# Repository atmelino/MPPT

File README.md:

# MPPT
Maximum Power Point Tracking Solar Powered Computer 

https://atmelino.github.io/MPPT/

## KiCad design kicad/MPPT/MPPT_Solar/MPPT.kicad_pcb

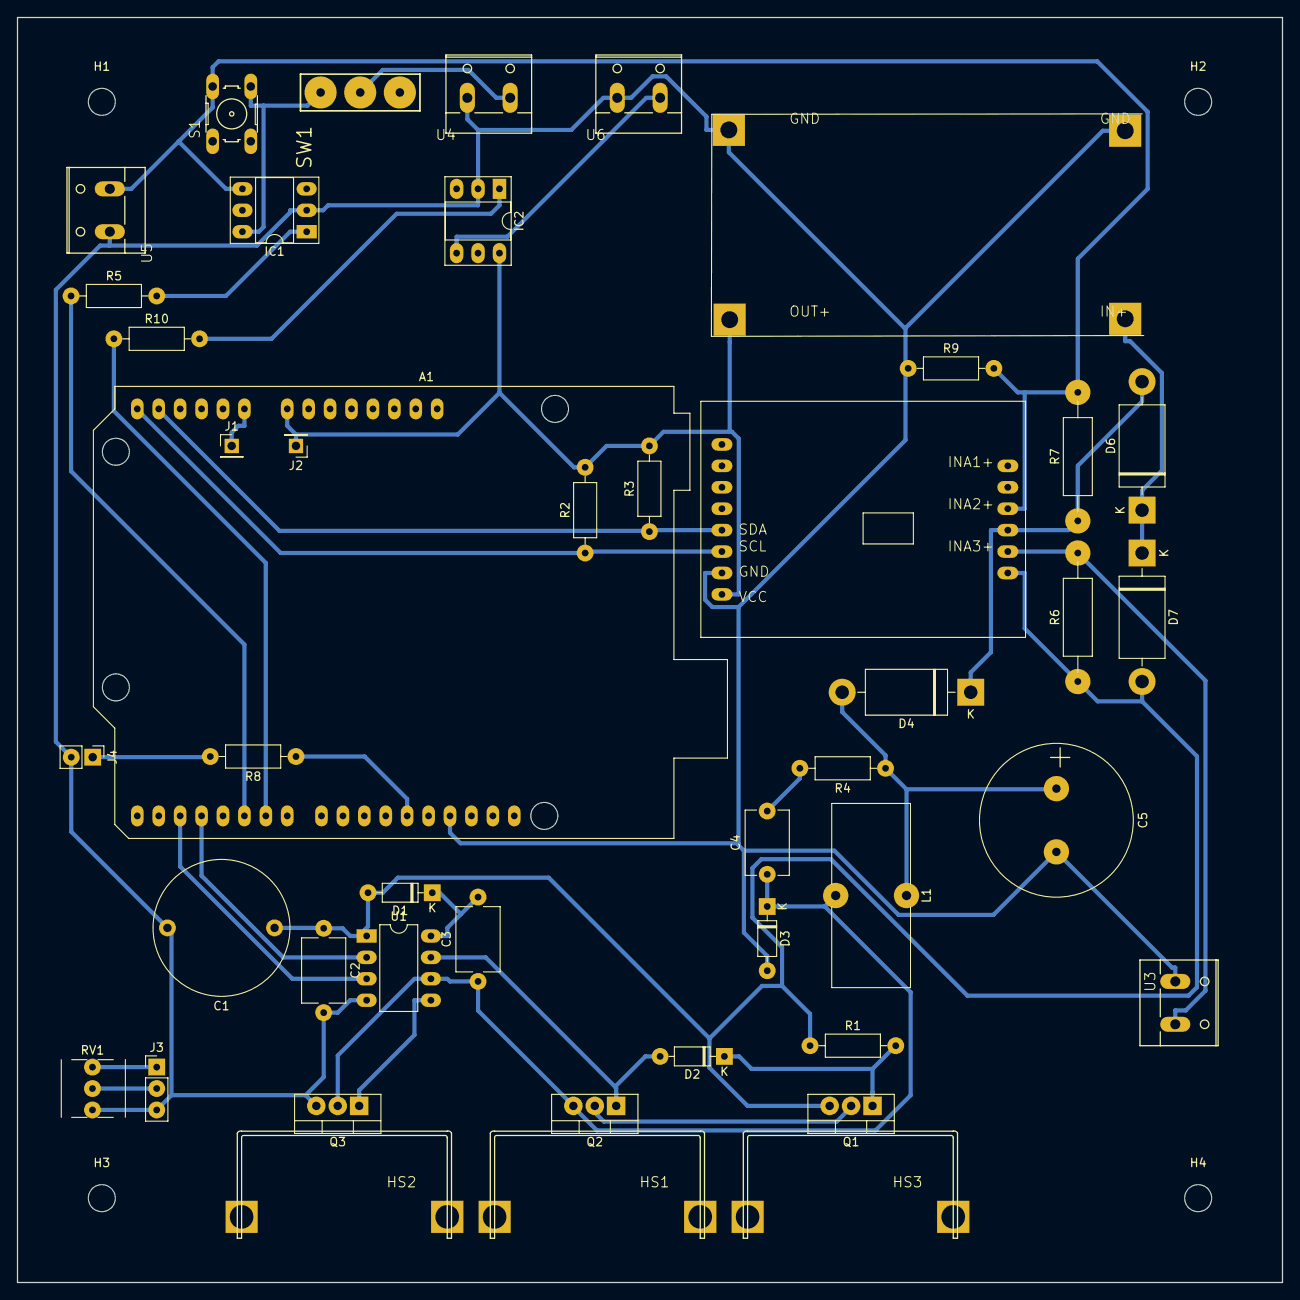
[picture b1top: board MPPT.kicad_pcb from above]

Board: 2 copper layers, 150.0 x 150.0 mm, 49 parts (0 on the bottom side), 31 nets.

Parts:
A1: Arduino_UNO_R3_mylib; Arduino_UNO_R3
C1: 1000uF/25V; C_Radial_D16.0mm_H25.0mm_P7.50mm_mod
C2, C3: 0.1uF; C_Disc_D7.5mm_W5.0mm_P10.00mm
C4: 0.1uF; C_Disc_D7.5mm_W5.0mm_P7.50mm
C5: 220uF/25V; C_Radial_D18.0mm_H35.5mm_P7.50mm
D1, D3: 1N4007; D_DO-35_SOD27_P7.62mm_Horizontal_fatpad
D2: 1N4148; D_DO-35_SOD27_P7.62mm_Horizontal_fatpad
D4, D6, D7: 1N5822; D_DO-201AD_P15.24mm_Horizontal
H1, H2, H3, H4: MountingHole; MountingHole_3.2mm_M3
HS1, HS2, HS3: Heatsink; WAKEFIELD265
IC1, IC2: AQV252G; DIP-6_W7.62mm_Socket_LongPads
J1, J2: Conn_01x01_Male; PinHeader_1x01_P2.54mm_Vertical
J3: Conn_01x03_Male; PinHeader_1x03_P2.54mm_Vertical
J4: Conn_01x02_Male; PinHeader_1x02_P2.54mm_Vertical_fatpad
L1: L; L_Toroid_Vertical_L21.6mm_W9.1mm_P8.40mm_Bourns_5700_fatpad
Q1, Q2, Q3: IRLZ44Z; TO-220-3_Vertical
R1: 470K; R_Axial_DIN0207_L6.3mm_D2.5mm_P10.16mm_Horizontal_fatpad
R2, R3: 4.7K; R_Axial_DIN0207_L6.3mm_D2.5mm_P10.16mm_Horizontal_fatpad
R4: 220; R_Axial_DIN0207_L6.3mm_D2.5mm_P10.16mm_Horizontal_fatpad
R5, R10: 2.2K; R_Axial_DIN0207_L6.3mm_D2.5mm_P10.16mm_Horizontal_fatpad
R6, R7: 0.1; R_Axial_DIN0309_L9.0mm_D3.2mm_P15.24mm_Horizontal_pad3mm
R8: 10K; R_Axial_DIN0207_L6.3mm_D2.5mm_P10.16mm_Horizontal_fatpad
R9: 100K; R_Axial_DIN0207_L6.3mm_D2.5mm_P10.16mm_Horizontal_fatpad
RV1: R_POT_TRIM; blue_trimpot
S1: switchpushadafruit; B3F-10XX
SW1: SW_SPDT; SWITCH-SPDT_0.185_INCH
U1: IR2104; DIP-8_W7.62mm_LongPads
U2: DROK_BUCKCONV_TWOSTORY_PADS
U3: Solar; W237-132
U4: Battery; W237-132
U5: 8V; W237-132
U6: 5V; W237-132
X2: SWITCHDOC_INA3221; SWITCHDOC_INA3221_NODRILL

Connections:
+5V: A1.8, IC2.6, J2.1, R2.2, R3.2, U2.OUT, X2.1
GND: A1.29, C1.2, C2.2, C5.2, D3.2, IC1.2, IC2.2, J3.3, J4.2, Q3.3, R9.1, RV1.3, U1.4, U2.GND_IN, U2.GND_OUT, U3.1, U4.1, U5.1, U6.1, X2.2
unnamed: A1.9, J1.1
unnamed: A1.13, R3.1, X2.4
unnamed: A1.14, R2.1, X2.3
unnamed: A1.17, U1.3
unnamed: A1.18, U1.2
unnamed: A1.20, R5.1
unnamed: A1.21, R10.1
unnamed: A1.27, R8.1
unnamed: C1.1, C2.1, D1.2, D7.2, Q1.3, R1.1, R6.1, U1.1, X2.9
unnamed: C3.1, C4.1, D3.1, L1.2, Q2.3, Q3.2, U1.6
unnamed: C3.2, D1.1, U1.8
unnamed: C4.2, R4.2
unnamed: C5.1, D4.2, L1.1, R4.1
unnamed: D2.1, Q1.1, R1.2
unnamed: D2.2, Q2.1, U1.7
unnamed: D4.1, D6.2, R7.1, X2.11
unnamed: D6.1, D7.1, U2.IN
unnamed: IC1.1, R5.2
unnamed: IC1.4, R7.2, R9.2, S1.2, U5.2, X2.12
unnamed: IC1.6, S1.4, SW1.1
unnamed: IC2.1, R10.2
unnamed: IC2.4, U6.2
unnamed: J3.1, RV1.1
unnamed: J3.2, RV1.2
unnamed: J4.1, R8.2
unnamed: Q1.2, Q2.2
unnamed: Q3.1, U1.5
unnamed: R6.2, U3.2, X2.10
unnamed: SW1.2, U4.2

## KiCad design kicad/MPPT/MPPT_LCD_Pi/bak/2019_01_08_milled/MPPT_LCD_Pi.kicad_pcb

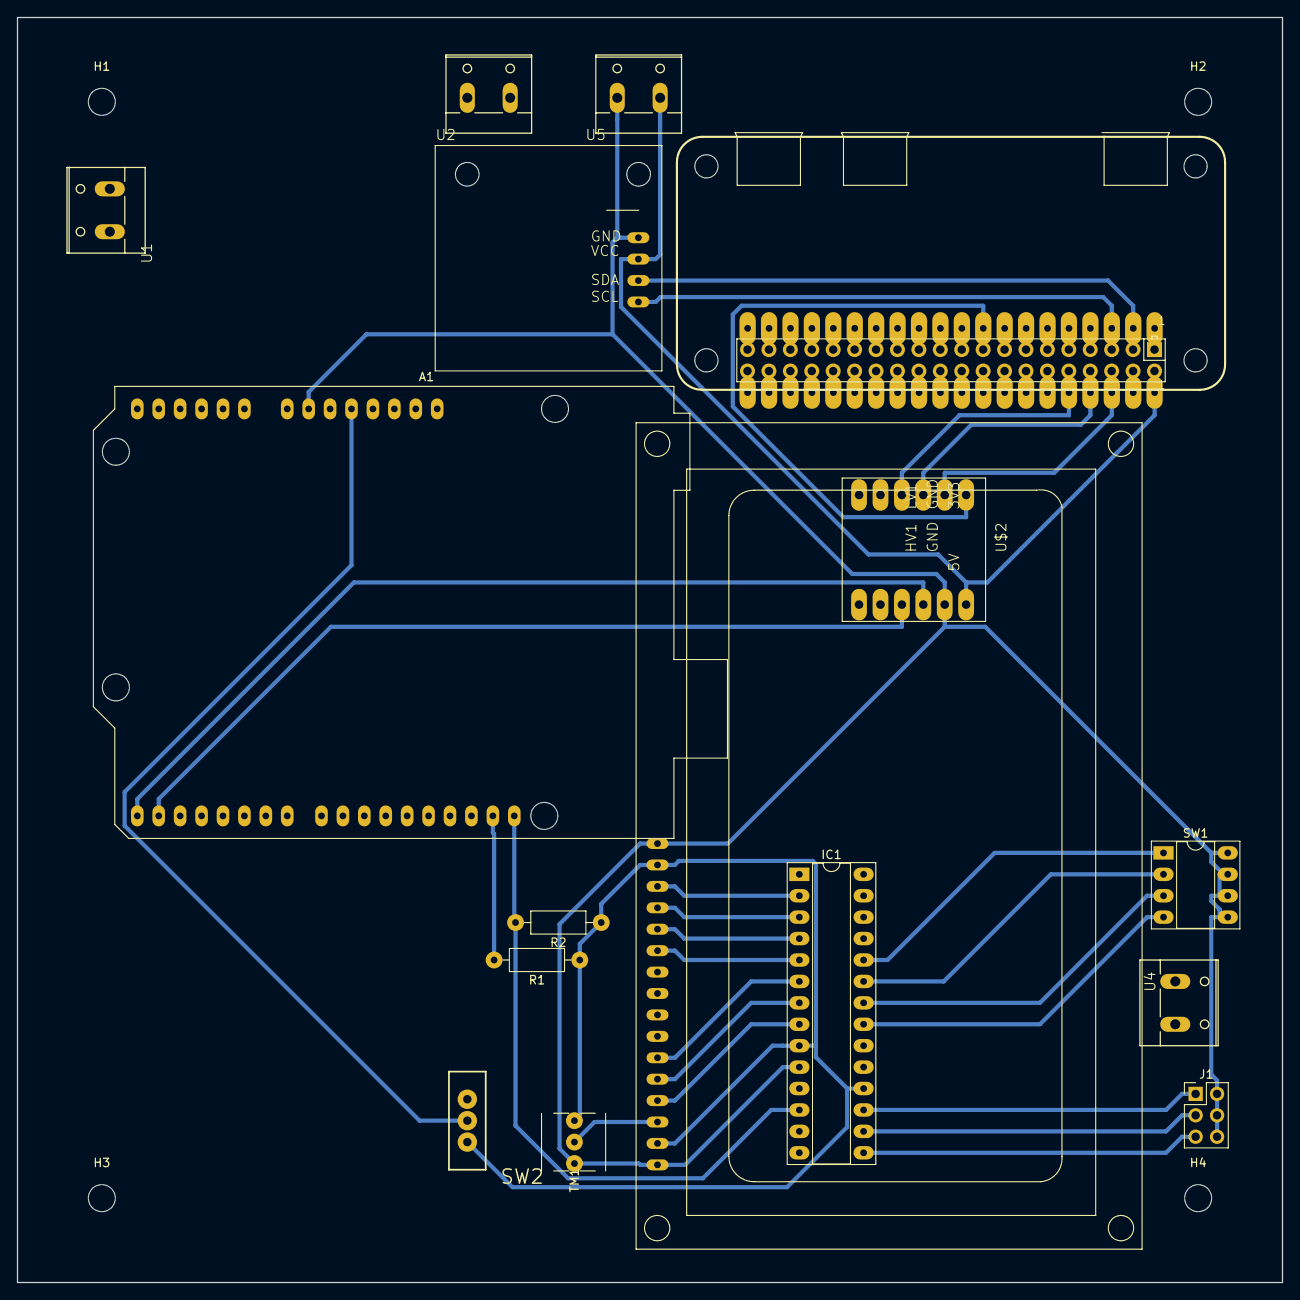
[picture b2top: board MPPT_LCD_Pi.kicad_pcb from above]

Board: 2 copper layers, 150.0 x 150.0 mm, 20 parts (0 on the bottom side), 62 nets.

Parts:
A1: Arduino_UNO_R3_mylib; Arduino_UNO_R3_WithMountingHoles_mylib
H1, H2, H3, H4: MountingHole; MountingHole_3.2mm_M3
IC1: MCP23017SP; DIP-28_W7.62mm_Socket_LongPads
J1: Conn_02x03_Odd_Even; PinHeader_2x03_P2.54mm_Vertical
R1, R2: 4.7K; R_Axial_DIN0207_L6.3mm_D2.5mm_P10.16mm_Horizontal_fatpad
SW1: SW_DIP_x04; DIP-8_W7.62mm_Socket_LongPads
SW2: SW_SPDT; SWITCH-SPDT
TM1: TRIMPOT; blue_trimpot
U1: 8V; W237-132_screw_terminal
U2: Battery; W237-132_screw_terminal
U4: Solar; W237-132_screw_terminal
U5: Pi; W237-132_screw_terminal
U$1: RPI-ZERO; RASPBERRYPI_V13_EXTRAPADS
U$2: LEVEL_SHIFTER
X1: ARDOKIT_DS1307RIGHT; ARDOKIT_DS1307_RIGHT
X2: HD44780LCD; LCD_40_04

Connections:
+3V3: U$1.17, U$1.17_LONG, U$2.1
+5V: IC1.9, IC1.18, R1.1, R2.1, SW2.1, TM1.3, X2.2, X2.15
/5V_Pi: U5.2, U$1.2, U$1.2_LONG, U$2.12, X1.VCC
GND: A1.7, IC1.10, J1.2, J1.4, J1.6, SW1.5, SW1.6, SW1.7, SW1.8, TM1.1, U5.1, U$2.11, X1.GND, X2.1, X2.16
unnamed: A1.5, SW2.2
unnamed: A1.15, U$2.10
unnamed: A1.16, U$2.9
unnamed: A1.31, R1.2
unnamed: A1.32, IC1.12, R2.2
unnamed: IC1.2, X2.14
unnamed: IC1.3, X2.13
unnamed: IC1.4, X2.12
unnamed: IC1.5, X2.11
unnamed: IC1.6, X2.6
unnamed: IC1.7, X2.5
unnamed: IC1.8, X2.4
unnamed: IC1.15, J1.5
unnamed: IC1.16, J1.3
unnamed: IC1.17, J1.1
unnamed: IC1.21, SW1.4
unnamed: IC1.22, SW1.3
unnamed: IC1.23, SW1.2
unnamed: IC1.24, SW1.1
unnamed: TM1.2, X2.3
unnamed: U$1.1, U$1.1_LONG
unnamed: U$1.3, U$1.3_LONG, X1.SDA
unnamed: U$1.4, U$1.4_LONG
unnamed: U$1.5, U$1.5_LONG, X1.SCL
unnamed: U$1.6, U$1.6_LONG, U$2.2
unnamed: U$1.7, U$1.7_LONG
unnamed: U$1.8, U$1.8_LONG, U$2.3
unnamed: U$1.9, U$1.9_LONG
unnamed: U$1.10, U$1.10_LONG, U$2.4
unnamed: U$1.11, U$1.11_LONG
unnamed: U$1.12, U$1.12_LONG
unnamed: U$1.13, U$1.13_LONG
unnamed: U$1.14, U$1.14_LONG
unnamed: U$1.15, U$1.15_LONG
unnamed: U$1.16, U$1.16_LONG
unnamed: U$1.18, U$1.18_LONG
unnamed: U$1.19, U$1.19_LONG
unnamed: U$1.20, U$1.20_LONG
unnamed: U$1.21, U$1.21_LONG
unnamed: U$1.22, U$1.22_LONG
unnamed: U$1.23, U$1.23_LONG
unnamed: U$1.24, U$1.24_LONG
unnamed: U$1.25, U$1.25_LONG
unnamed: U$1.26, U$1.26_LONG
unnamed: U$1.27, U$1.27_LONG
unnamed: U$1.28, U$1.28_LONG
unnamed: U$1.29, U$1.29_LONG
unnamed: U$1.30, U$1.30_LONG
unnamed: U$1.31, U$1.31_LONG
unnamed: U$1.32, U$1.32_LONG
unnamed: U$1.33, U$1.33_LONG
unnamed: U$1.34, U$1.34_LONG
unnamed: U$1.35, U$1.35_LONG
unnamed: U$1.36, U$1.36_LONG
unnamed: U$1.37, U$1.37_LONG
unnamed: U$1.38, U$1.38_LONG
unnamed: U$1.39, U$1.39_LONG
unnamed: U$1.40, U$1.40_LONG

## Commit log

2019-01-29 web page
2019-01-29 kicad files
2019-01-29 index
2019-01-30 import Arduino
2019-01-30 import raspberry pi
2019-01-30 new autostart directory
2019-01-30 date set
2019-01-31 set date
2019-01-31 set clock
2019-01-31 cleanup
2019-01-31 log file option
2019-02-01 debug msg
2019-02-01 log file period
2019-02-02 log period
2019-02-04 reinstall PC simulation
2019-02-05 show buffer length
2019-02-06 RTC error message
2019-02-06 clock RTC or PC
2019-02-06 RTC clock for rPi
2019-02-06 data files in folders
2019-02-06 sim to rPi
2019-02-06 show/hide file selector
2019-02-06 sort data by year, month
2019-02-07 file list on startup
2019-02-07 stored data years combobox
2019-02-10 display actual PWM
2019-02-14 debug messages
2019-02-15 3.3 Volt
2019-02-24 webserver
2019-02-25 I2C and INA3221
2019-02-26 INA3221 and STM32
2019-02-27 INA3221
2019-02-27 print INA3221 values as hex
2019-02-28 3 channels
2019-02-28 channels
2019-03-01 module
2019-03-04 module load from disk
2019-03-08 reorganize by versions, docs
2019-03-09 Ds1307
2019-03-10 docs
2019-03-11 charge LED
2019-03-12 autostart
2019-03-14 sd card
2019-03-15 LED's
2019-03-16 development docs
2019-03-16 clock
2019-03-17 buck circuit
2019-03-18 wifi
2019-03-19 console.log stalls program
2019-03-19 relay
2019-03-24 table JSON
2019-03-25 table
2019-03-26 RTC set
2019-03-27 clock, settings
2019-04-02 PWM off when no solar
2019-04-03 pwm and frequency when solar off
2019-04-04 settings
2019-04-04 battery protection
2019-04-07 voltages
2019-04-10 SD card issues
2019-04-10 data file
2019-04-11 SD card issue
2019-04-11 battery connect
2019-04-12 sub-directories
2019-04-13 traverse folders
2019-04-14 file access
2019-04-14 date string
2019-04-15 SD card Arduino
2019-04-16 data files
2019-04-16 memory issue
2019-04-17 web page on SD card
2019-04-17 web site on SD card
2019-04-17 table columns
2019-04-19 serial
2019-04-20 serial read
2019-04-20 serial comm
2019-04-21 flash
2019-04-22 hex dump
2019-04-22 hex dump pages of flash
2019-04-22 flash memory tests
2019-04-22 html to flash
2019-04-23 web server http
2019-04-23 server
2019-04-23 serve in parts
2019-04-23 multiple flash pages
2019-04-23 flash pages for web page
2019-04-24 write loop
2019-04-24 save web page
2019-04-24 web socket closes
2019-04-25 web page send in parts
2019-04-25 web page load timing
2019-04-25 load javascript file separately
2019-04-26 faster Flash read
2019-04-26 server consider all requests
2019-04-26 full web page from external flash
2019-04-27 flash read performance
2019-04-27 working on flash sector modify
2019-04-27 read and write sector
2019-04-28 update log
2019-04-28 faster write
2019-04-28 log write and read
2019-04-28 run without IDE and console
2019-04-29 flash ID
2019-04-29 start version 3
2019-04-30 comment
2019-04-30 copy node files
2019-04-30 INA3221 module
2019-05-01 date
2019-05-01 multiple I2C devices
2019-05-01 data line
2019-05-01 send data to client
2019-05-01 relay pin
2019-05-01 LED pins
2019-05-02 LED battery level indicators
2019-05-02 LED indicators
2019-05-03 battery PWM conditions
2019-05-04 save data files
2019-05-05 write data files
2019-05-07 low battery shutdown
2019-05-07 battery
2019-08-28 package lock security issue
2019-08-28 ESP32 initial
2019-09-02 wifi test
2019-09-02 wifi connected LED
2019-09-05 PWM and INA3221
2019-09-05 PWM enable pin, web wifi
2019-09-07 websocket
2019-09-09 JSON MPPT
2019-09-10 data table
2019-09-11 websocket send
2019-09-16 websocket PWM
2019-09-17 web PWM set
2019-09-18 PWM control
2019-09-19 file save
2019-09-19 SD card save
2019-09-21 settings in SPIFFS
2019-09-21 restore settings from SPIFFS
2019-09-23 update settings dialog
2019-09-23 data save period
2019-09-24 measurements to save
2019-09-25 file read
2019-09-26 years directory
2019-09-27 year list
2019-09-28 get years dir
2019-09-29 months dir on SD
2019-09-30 list data files
2019-09-30 days list
2019-10-01 read data file
2019-10-02 send file data
2019-10-03 String for file data
2019-10-03 String in get Dir
2019-10-05 write data file
2019-10-07 batt level indicator
2019-10-09 new PCB
2019-10-12 INA channels
2019-10-13 power indicator LEDs
2019-10-14 battery relay
2019-10-14 PWM half bridge driver on off
2019-10-28 clean up
2020-03-17 Bump minimist in /version3_0/raspberryPi/develop/INA3221
    Bumps [minimist](https://github.com/substack/minimist) from 1.2.0 to 1.2.5.
    - [Release notes](https://github.com/substack/minimist/releases)
    - [Commits](https://github.com/substack/minimist/compare/1.2.0...1.2.5)
2020-12-11 Bump ini from 1.3.5 to 1.3.8 in /version3_0/raspberryPi/develop/INA3221
    Bumps [ini](https://github.com/isaacs/ini) from 1.3.5 to 1.3.8.
    - [Release notes](https://github.com/isaacs/ini/releases)
    - [Commits](https://github.com/isaacs/ini/compare/v1.3.5...v1.3.8)
2021-06-10 Bump normalize-url in /version3_0/raspberryPi/develop/INA3221
    Bumps [normalize-url](https://github.com/sindresorhus/normalize-url) from 4.5.0 to 4.5.1.
    - [Release notes](https://github.com/sindresorhus/normalize-url/releases)
    - [Commits](https://github.com/sindresorhus/normalize-url/commits)
    ---
    updated-dependencies:
    - dependency-name: normalize-url
2022-04-11 Bump minimist in /version3_0/raspberryPi/develop/INA3221
    Bumps [minimist](https://github.com/substack/minimist) from 1.2.0 to 1.2.6.
    - [Release notes](https://github.com/substack/minimist/releases)
    - [Commits](https://github.com/substack/minimist/compare/1.2.0...1.2.6)
    ---
    updated-dependencies:
    - dependency-name: minimist
2022-12-06 Bump qs and express in /version3_0/raspberryPi/MPPT
    Bumps [qs](https://github.com/ljharb/qs) to 6.11.0 and updates ancestor dependency [express](https://github.com/expressjs/express). These dependencies need to be updated together.
    Updates `qs` from 6.7.0 to 6.11.0
    - [Release notes](https://github.com/ljharb/qs/releases)
    - [Changelog](https://github.com/ljharb/qs/blob/main/CHANGELOG.md)
    - [Commits](https://github.com/ljharb/qs/compare/v6.7.0...v6.11.0)
    Updates `express` from 4.17.1 to 4.18.2
2022-12-10 Bump express from 4.17.1 to 4.17.3 in /version3_0/raspberryPi/MPPT
    Bumps [express](https://github.com/expressjs/express) from 4.17.1 to 4.17.3.
    - [Release notes](https://github.com/expressjs/express/releases)
    - [Changelog](https://github.com/expressjs/express/blob/master/History.md)
    - [Commits](https://github.com/expressjs/express/compare/4.17.1...4.17.3)
    ---
    updated-dependencies:
